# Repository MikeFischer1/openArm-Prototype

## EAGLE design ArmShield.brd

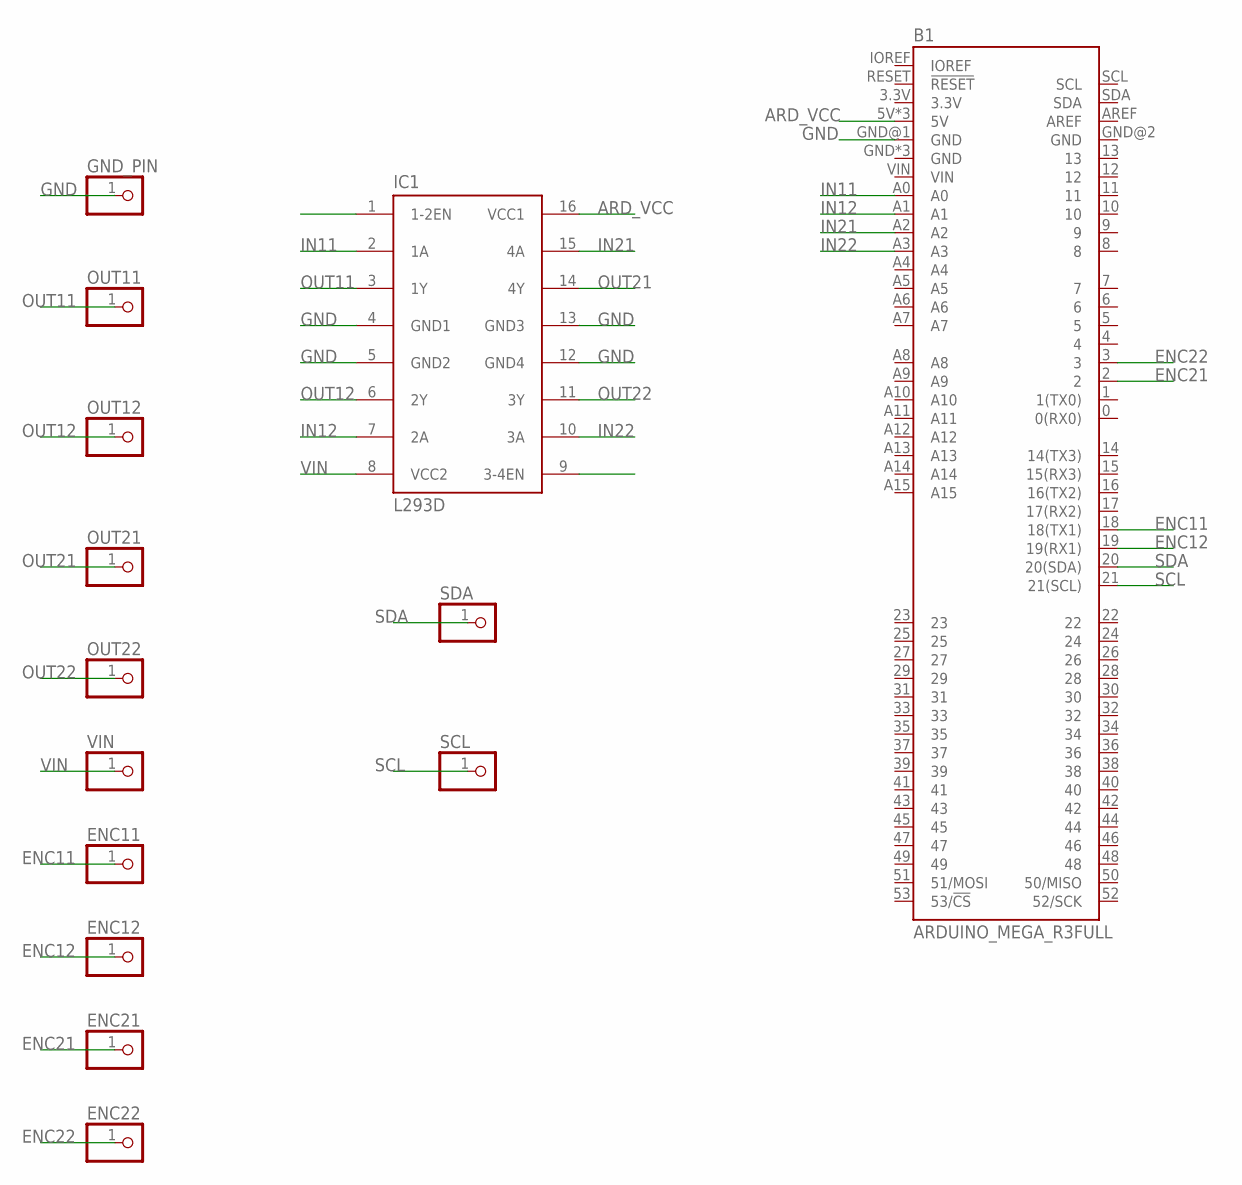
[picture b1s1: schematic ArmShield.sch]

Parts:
B1: ARDUINO_MEGA_R3FULL; ARDUINO_MEGA_NO_SILK
ENC11, ENC12, ENC21, ENC22: PINHD-1X1; 1X01
GND_PIN: PINHD-1X1; 1X01
IC1: L293D; DIL16
OUT11, OUT12, OUT21, OUT22: PINHD-1X1; 1X01
SCL: PINHD-1X1; 1X01
SDA: PINHD-1X1; 1X01
VIN: PINHD-1X1; 1X01

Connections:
ARD_VCC: B1.5V, B1.5V@1 (5V), B1.5V@2 (5V), IC1.16 (VCC1)
ENC11: B1.18 (18(TX1)), ENC11.1
ENC12: B1.19 (19(RX1)), ENC12.1
ENC21: B1.2, ENC21.1
ENC22: B1.3, ENC22.1
GND: B1.GND@1 (GND), GND_PIN.1, IC1.4 (GND1), IC1.5 (GND2), IC1.12 (GND4), IC1.13 (GND3)
IN11: B1.A0, IC1.2 (1A)
IN12: B1.A1, IC1.7 (2A)
IN21: B1.A2, IC1.15 (4A)
IN22: B1.A3, IC1.10 (3A)
OUT11: IC1.3 (1Y), OUT11.1
OUT12: IC1.6 (2Y), OUT12.1
OUT21: IC1.14 (4Y), OUT21.1
OUT22: IC1.11 (3Y), OUT22.1
SCL: B1.21 (21(SCL)), SCL.1
SDA: B1.20 (20(SDA)), SDA.1
VIN: IC1.8 (VCC2), VIN.1

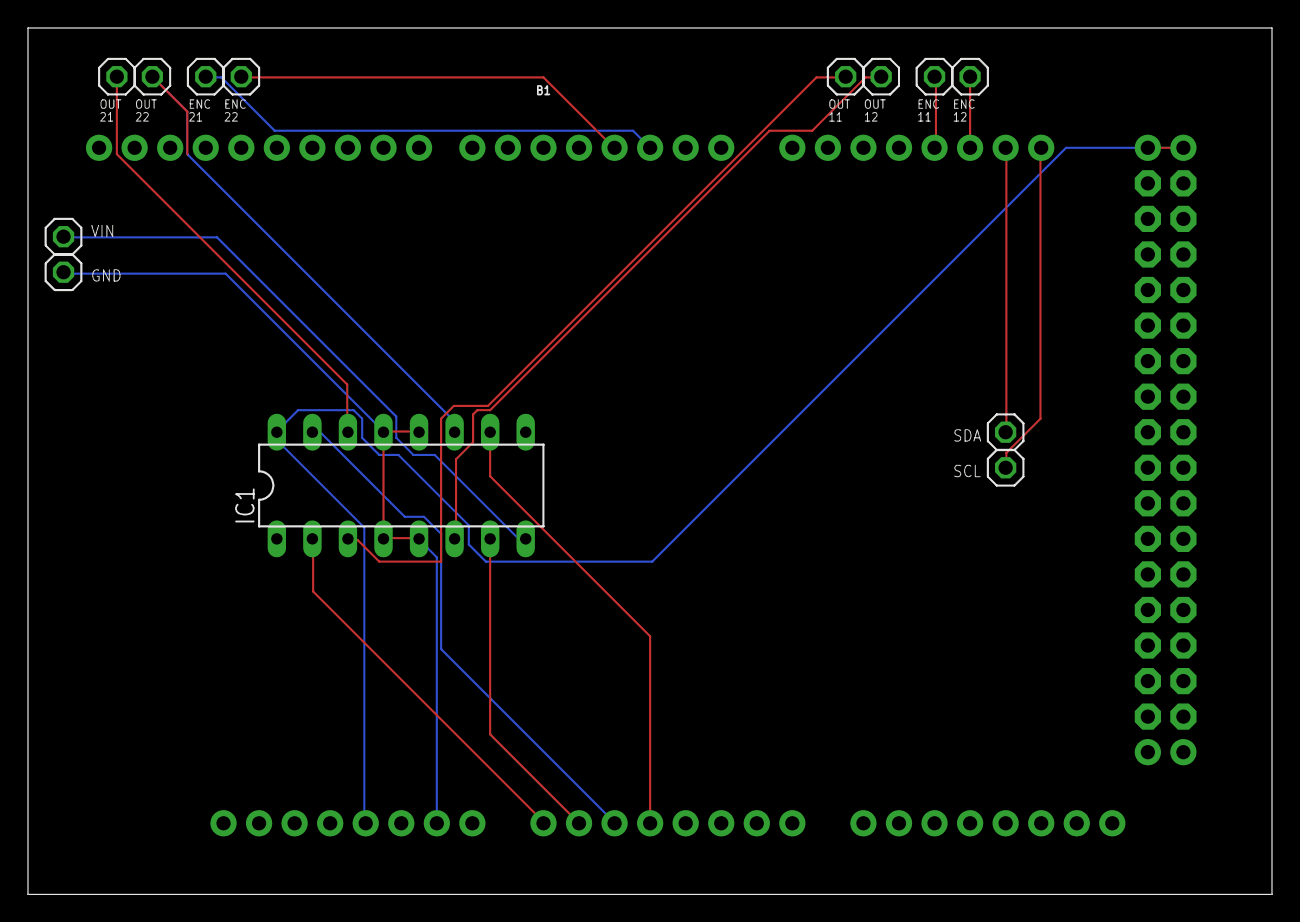
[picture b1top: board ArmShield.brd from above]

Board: 2 copper layers, 88.9 x 61.9 mm, 14 parts (0 on the bottom side), 17 nets.

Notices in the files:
parts and their libraries:
SparkFun-Boards: Licensing: Creative Commons ShareAlike 4.0 International - https://creativecommons.org/licenses/by-sa/4.0
